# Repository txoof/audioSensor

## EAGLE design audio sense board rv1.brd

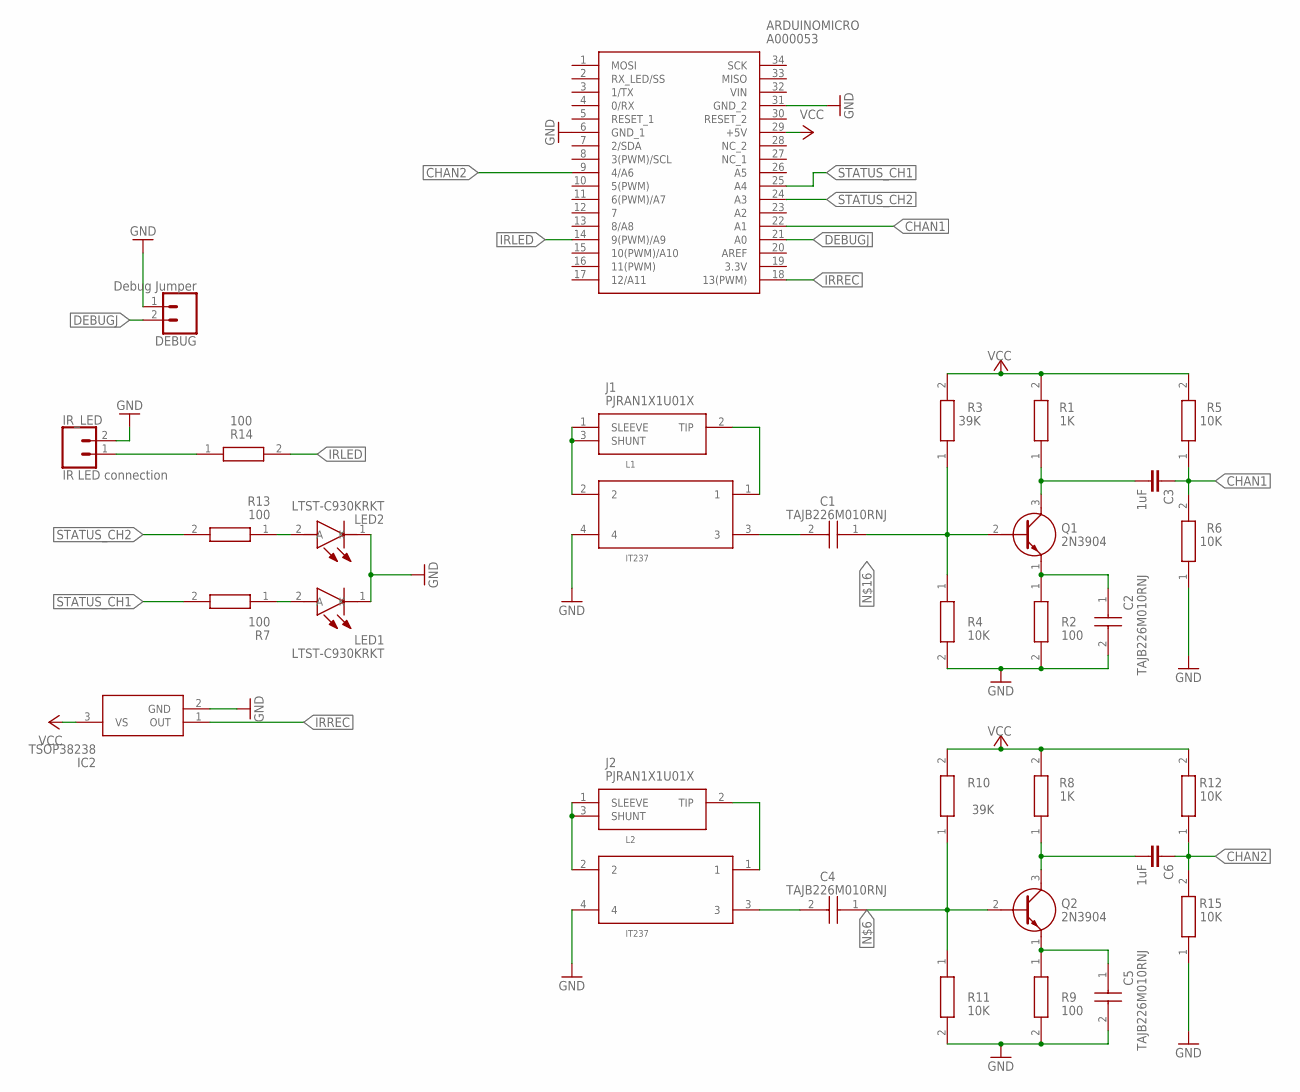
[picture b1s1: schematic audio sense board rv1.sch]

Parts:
ARDUINOMICRO: A000053; HDRV34W70P1570X254_2X17_4900X1
C1, C2, C4, C5: TAJB226M010RNJ; CAPPM3528X210N
C3, C6: 1uF; CAP-PTH-2.54
DEBUG: Debug Jumper; 1X02_LOCK
IC2: TSOP38238
IR_LED: IR LED connection; 1X02_LOCK
J1, J2: PJRAN1X1U01X
L1, L2: IT237
LED1, LED2: LTST-C930KRKT; LTSTC930KRKT
Q1, Q2: 2N3904; CS_TO-92
R1, R8: 1K; RESC3116X70N
R2, R7, R9, R13, R14: 100; RESC3116X70N
R3, R10: 39K; RESC3116X70N
R4, R5, R6, R11, R12, R15: 10K; RESC3116X70N

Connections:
CHAN1: ARDUINOMICRO.22 (A1), C3.1, R5.1, R6.2
CHAN2: ARDUINOMICRO.9 (4/A6), C6.1, R12.1, R15.2
DEBUGJ: ARDUINOMICRO.21 (A0), DEBUG.2
GND: ARDUINOMICRO.6 (GND_1), ARDUINOMICRO.31 (GND_2), C2.2 (-), C5.2 (-), DEBUG.1, IC2.2 (GND), IR_LED.2, L1.4, L2.4, LED1.1 (K), LED2.1 (K), R2.2, R4.2, R6.1, R9.2, R11.2, R15.1
IRLED: ARDUINOMICRO.14 (9(PWM)/A9), R14.2
IRREC: ARDUINOMICRO.18 (13(PWM)), IC2.1 (OUT)
unnamed: J2.1 (SLEEVE), J2.3 (SHUNT), L2.2
unnamed: LED2.2 (A), R13.1
unnamed: J2.2 (TIP), L2.1
unnamed: LED1.2 (A), R7.1
unnamed: C4.2 (-), L2.3
unnamed: C4.1 (+), Q2.2 (B), R10.1, R11.1
unnamed: C5.1 (+), Q2.1 (E), R9.1
unnamed: C6.2, Q2.3 (C), R8.1
unnamed: IR_LED.1, R14.1
unnamed: J1.1 (SLEEVE), J1.3 (SHUNT), L1.2
unnamed: J1.2 (TIP), L1.1
unnamed: C1.1 (+), Q1.2 (B), R3.1, R4.1
unnamed: C1.2 (-), L1.3
unnamed: C2.1 (+), Q1.1 (E), R2.1
unnamed: C3.2, Q1.3 (C), R1.1
STATUS_CH1: ARDUINOMICRO.25 (A4), R7.2
STATUS_CH2: ARDUINOMICRO.24 (A3), R13.2
VCC: ARDUINOMICRO.29 (+5V), IC2.3 (VS), R1.2, R3.2, R5.2, R8.2, R10.2, R12.2

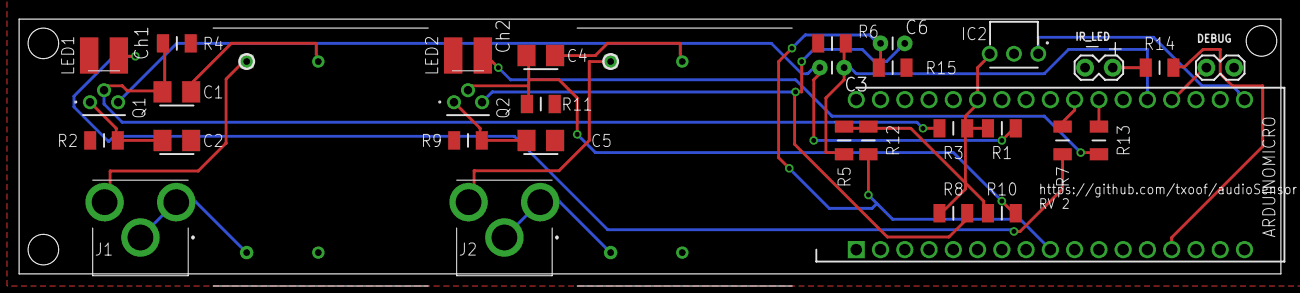
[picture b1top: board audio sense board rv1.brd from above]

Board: 2 copper layers, 132.1 x 26.7 mm, 33 parts (0 on the bottom side), 24 nets.

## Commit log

2019-04-02 add url to board
2019-04-02 add ground pour on bottom
2019-04-02 add CAM outputs
2019-04-02 rework led and signals
2019-04-07 rework of circuit, remove LEDs from amp circuit
2019-04-07 no air wires, fully routed
2019-04-07 no air wires, fully routed, smaller board
2019-04-09 update resistors, corners
2019-04-10 match LED names to channel names
2019-04-15 add transformers
2019-04-19 correcting issue - voltage divider in wrong location in both channels
2019-04-19 remove improper components, rework circuit
2019-04-19 update lable positions
2019-04-28 update component values on output LEDs
2019-04-28 add holes
2019-04-29 update silk screen layers
2019-04-29 move labels
2019-05-16 fix critical short on R4, overlaps and wire stubs
2019-05-16 increase pad size for all resistors
2019-05-19 minor changes
2019-05-19 update pad sizes
2019-06-01 update pads R14
2019-06-01 increase clearance on transformer and C2 pad
2019-06-01 update revision number - rv2

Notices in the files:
parts and their libraries:
SparkFun-Capacitors: Licensing: Creative Commons ShareAlike 4.0 International - https://creativecommons.org/licenses/by-sa/4.0
